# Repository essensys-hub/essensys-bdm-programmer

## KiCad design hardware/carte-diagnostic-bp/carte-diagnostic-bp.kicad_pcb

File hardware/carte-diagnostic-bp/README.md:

# Carte de diagnostic BP

Carte de banc : accès BDM au BP (J33, nappe 10 broches), écoute passive du bus I2C BP↔BA et analyseur 8 voies, derrière un seul port USB-C.

Spécification : `openspec/changes/carte-diagnostic-bp-2026-11-009/`.

**Prototype.** La carte finale est spécifiée par essensys-hub/essensys-i2c-ba-sniffer#10 ; celle-ci sert à valider les connecteurs, la protection 15 V, l'assemblage JLCPCB et la lecture BDM par la nappe.

| Fichier | Rôle |
|---|---|
| `gen_sch.py` | Décrit le circuit (table broche → net) et génère `carte-diagnostic-bp.kicad_sch` |
| `carte-diagnostic-bp.kicad_sch` | Schéma KiCad 10, à ouvrir avec le projet `.kicad_pro` |
| `gen_pcb.py`, `route_pcb.py`, `close_gaps.py` | Placement, routage et finition de `carte-diagnostic-bp.kicad_pcb` |
| `export_fab.py` | Gerber, perçages, nomenclature et placement au format JLCPCB |
| `check_netlist.py` | Invariants de sécurité contrôlés sur la netlist exportée |
| `nomenclature.md` | Références LCSC, stock et prix relevés |
| `protection-port-i2c.md` | Calcul de la protection 15 V du port I2C |

## Variantes

| Variante | Fichiers | Pico | USB |
|---|---|---|---|
| Base | `carte-diagnostic-bp.*` | Soudé à plat (pastilles crénelées et TP2/TP3) | Un seul USB-C, hub CH334R vers le Pico et l'analyseur |
| À trous (`CARTE_VARIANTE=tht`) | `carte-diagnostic-bp-tht.*` | Sur broches traversantes, remplaçable | Deux câbles : le micro-USB du Pico et l'USB-C de la carte pour l'analyseur |

La variante à trous n'a ni hub ni son quartz (61 composants au lieu de 66). Le VBUS de la carte ne rejoint pas le Pico : les deux moitiés ont chacune leur alimentation USB et seules les masses sont communes. Les résistances de prise de l'analyseur passent de 1 kΩ à 10 kΩ, pour qu'une moitié éteinte ne soit pas réalimentée par les signaux de l'autre. Elle ne satisfait pas l'exigence « un seul port USB » de la spécification.

Chaque script prend la variante dans la variable d'environnement `CARTE_VARIANTE` (vide ou `tht`).

## Régénérer et contrôler

    python3 hardware/carte-diagnostic-bp/gen_sch.py
    kicad-cli sch erc --severity-all --exit-code-violations hardware/carte-diagnostic-bp/carte-diagnostic-bp.kicad_sch
    pytest tests/test_carte_diagnostic_netlist.py

## Router la carte

    KPY=/Applications/KiCad/KiCad.app/Contents/Frameworks/Python.framework/Versions/3.9/bin/python3
    kicad-cli sch export netlist --format kicadsexpr -o /tmp/carte.net hardware/carte-diagnostic-bp/carte-diagnostic-bp.kicad_sch
    $KPY hardware/carte-diagnostic-bp/gen_pcb.py /tmp/carte.net            # empreintes, nets, placement, plans internes
    $KPY hardware/carte-diagnostic-bp/route_pcb.py freerouting-2.5.0.jar   # routage Freerouting, plans de masse externes
    $KPY hardware/carte-diagnostic-bp/close_gaps.py                        # ferme les dernières liaisons sous contrôle du DRC

Le routage automatique n'est pas reproductible à l'identique : `carte-diagnostic-bp.kicad_pcb` est versionné tel que routé, et la CI contrôle son DRC sans le régénérer.

## Dossier de fabrication JLCPCB

    python3 hardware/carte-diagnostic-bp/export_fab.py

Le dossier `fab/` (non versionné, publié comme artefact par la CI) contient `gerbers.zip`, `bom-jlcpcb.csv` et `cpl-jlcpcb.csv`. Options de commande : 4 couches, 1,6 mm, assemblage de la face avant. Dans l'outil de commande, contrôler l'aperçu du placement : les rotations viennent de KiCad et certaines pièces (SOT-23, SOT-223, QFN, USB-C) peuvent demander une correction.

Six composants ne sont pas assemblés par JLCPCB (`fab/a-souder-a-la-main.csv`) : le module Pico, l'embase de la nappe, les deux embases I2C, le connecteur SWD et le bouton BOOTSEL, dont la référence reste à figer. Un RP2040 dont la flash est vierge démarre seul en mode de chargement USB : le bouton ne sert qu'aux rechargements suivants.

## État

Les deux variantes font 100 × 60 mm en 4 couches et ont été routées le 2026-11-15 : DRC à 0 violation et 0 liaison manquante, pastilles conformes à la netlist du schéma (301 pour la base, 266 pour la variante à trous). Les repères des petits composants (R, C, D, F) ne sont pas sérigraphiés.

Le routage sort d'un routeur automatique et **doit être relu avant toute commande** : paire USB non routée en différentiel, position du quartz, découplage. Le dossier de fabrication se génère, mais il n'a pas encore été chargé dans l'outil de commande JLCPCB.

Sur la carte de base, les pastilles TP2 et TP3 du module Pico sont sous le module : elles demandent de la pâte à braser et de l'air chaud, ou un perçage de la carte à ajouter.

Défaut connu : le connecteur USB-C (J1) est en retrait d'environ 0,5 mm du bord de la carte ; certains câbles peuvent buter. À rapprocher du bord à la prochaine révision. Dans l'outil JLCPCB, J1 doit aussi être remonté d'environ 1,5 mm pour tomber sur ses pastilles.

À confirmer avant la commande :

- fiche technique du hub CH334R : quartz 12 MHz et broche `RESET/CDP` ;
- empreinte des embases I2C, à confronter au plan Würth 66200421122 (empreinte Micro-Fit 3.0 provisoire) ;
- empreinte du connecteur USB-C KH-TYPE-C-16P ;
- chaîne de capture RP2040 (tâche 1.2).

Sur la carte de base, le micro-USB du module Pico ne doit jamais être branché : son USB passe par les pastilles TP2 et TP3 vers le hub.

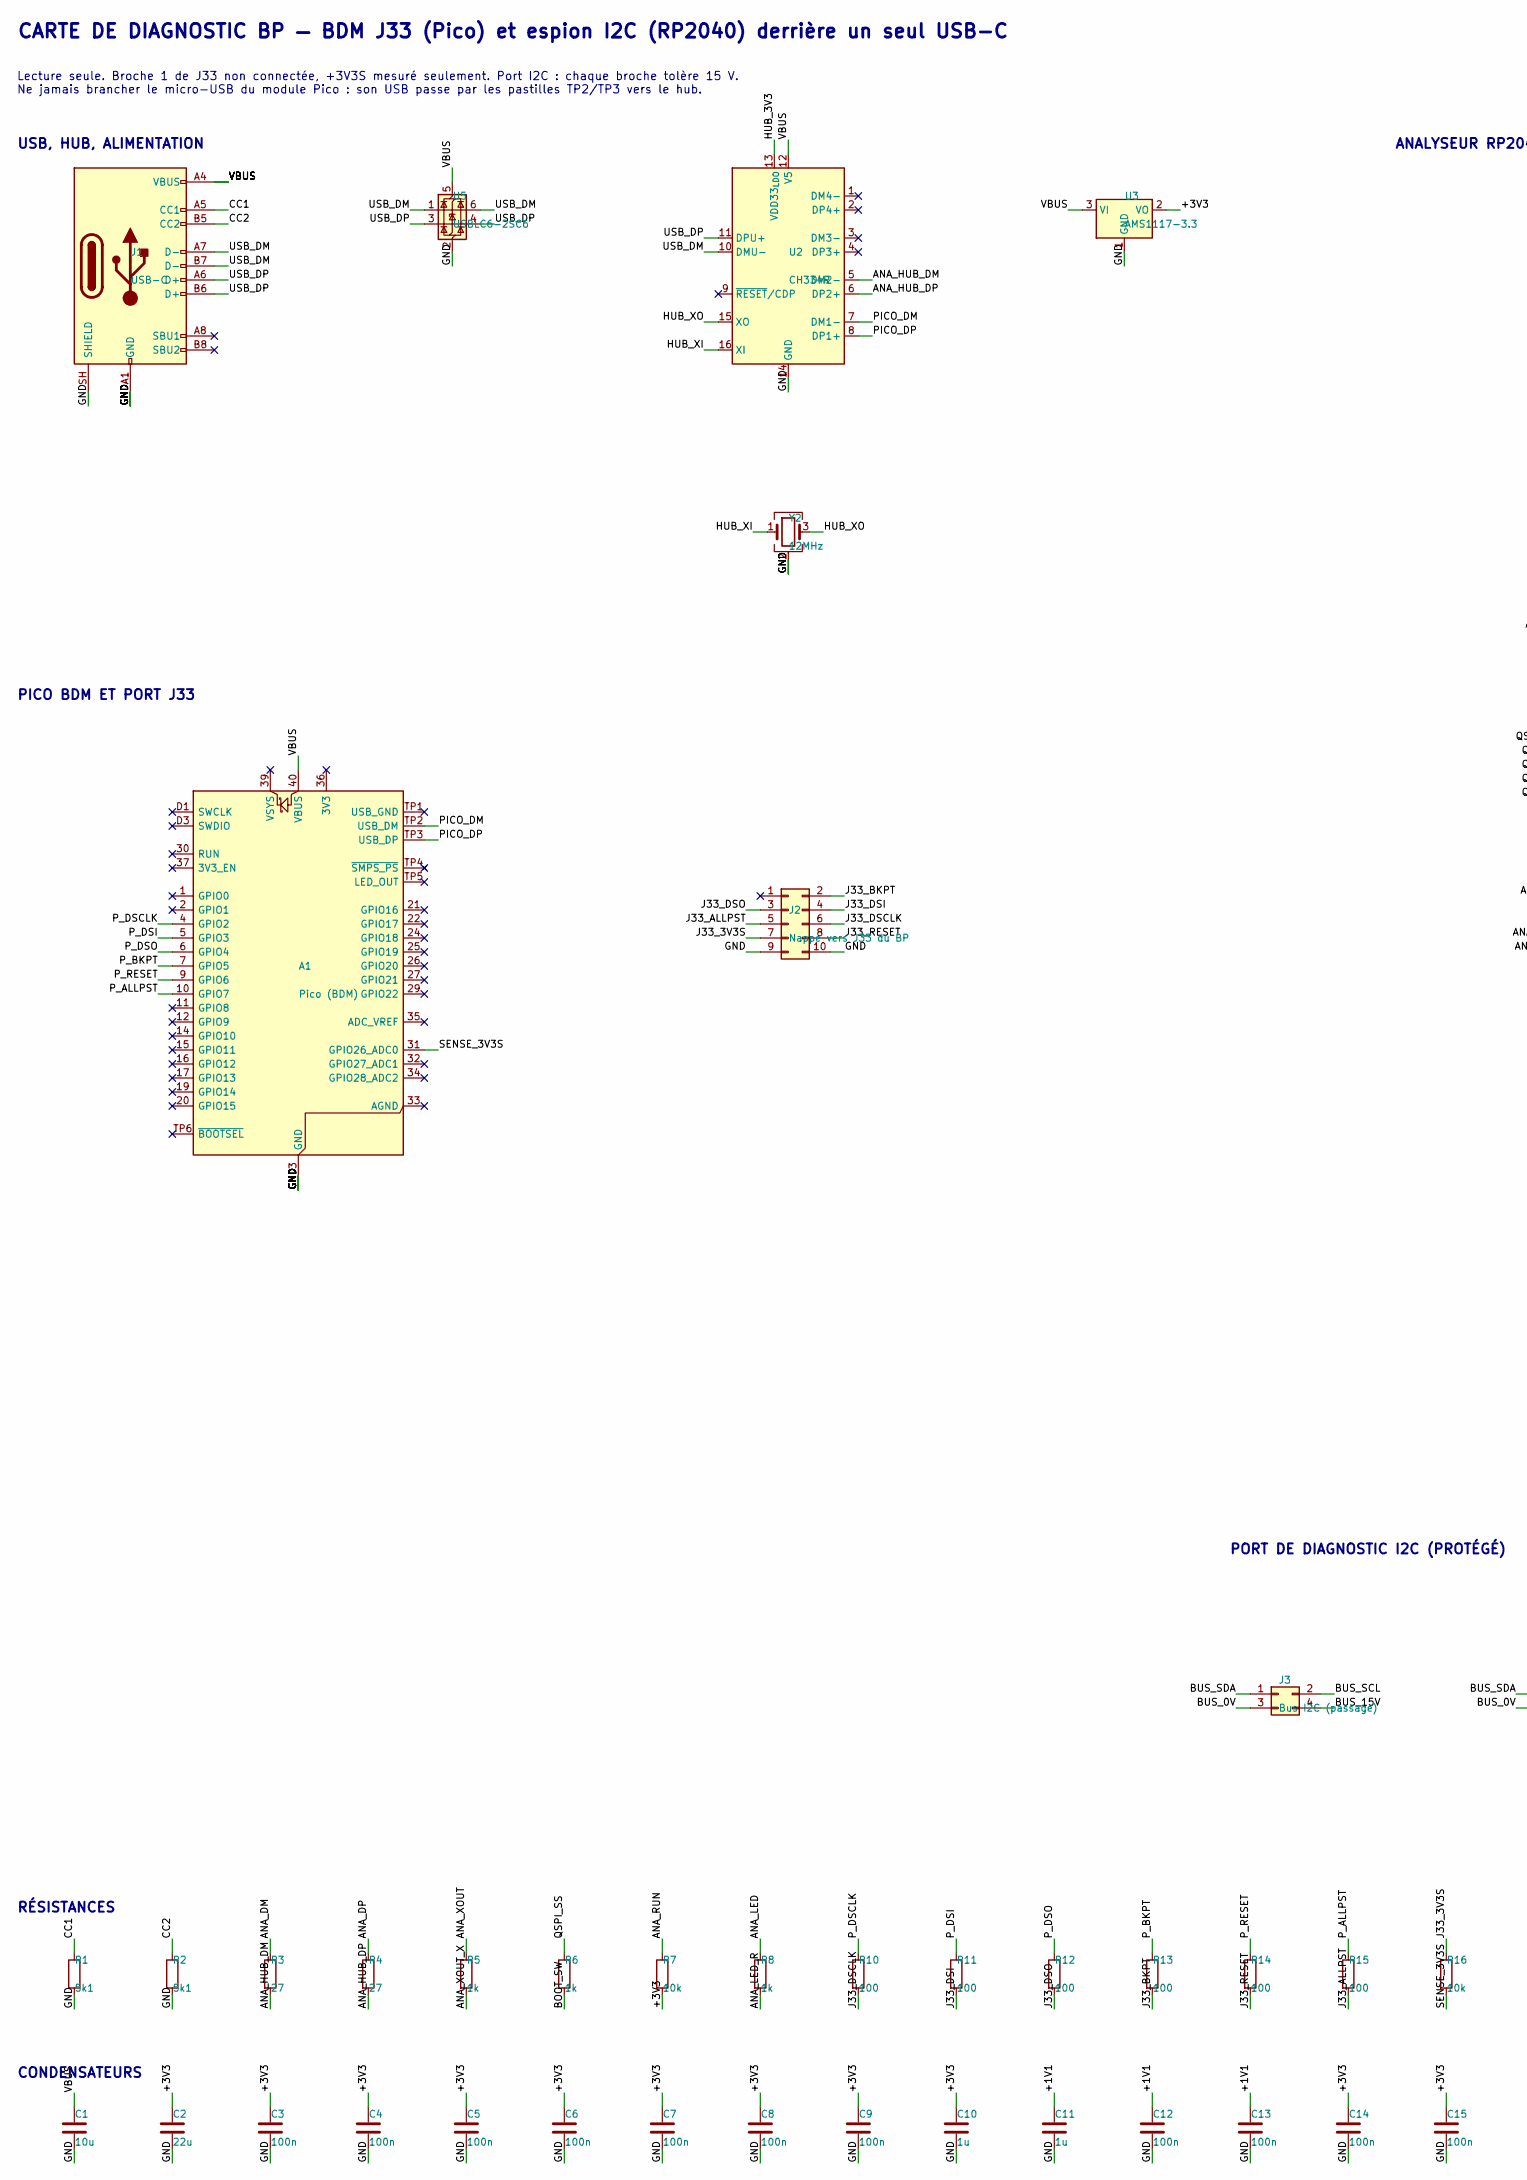
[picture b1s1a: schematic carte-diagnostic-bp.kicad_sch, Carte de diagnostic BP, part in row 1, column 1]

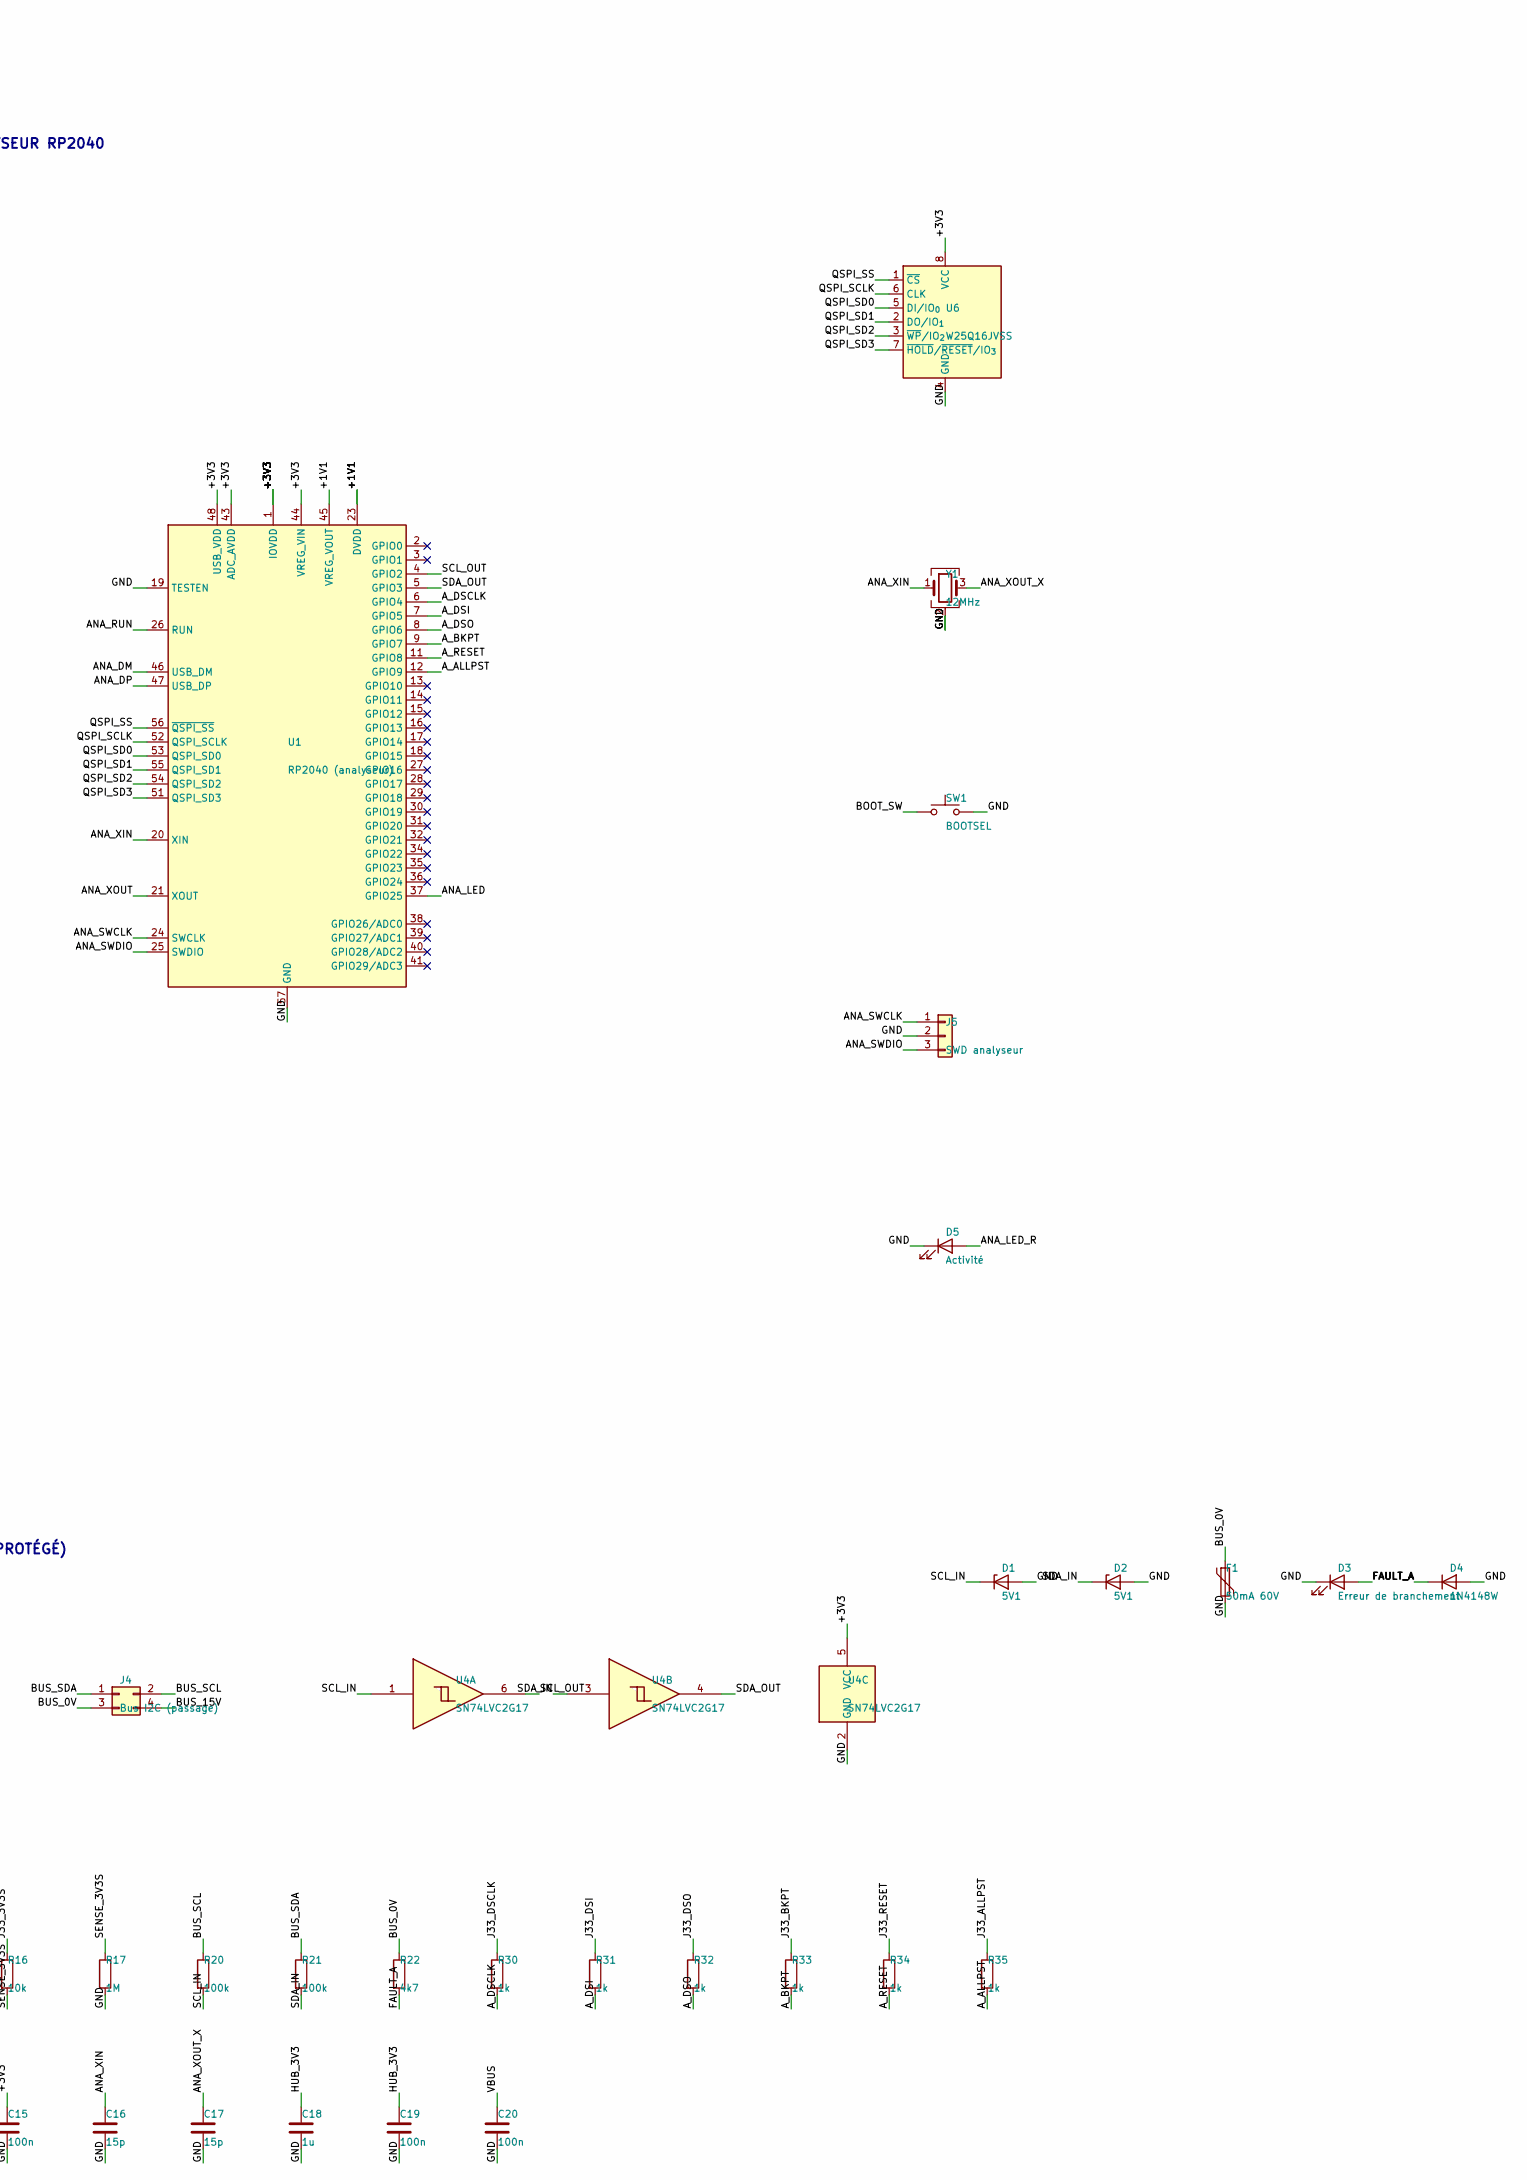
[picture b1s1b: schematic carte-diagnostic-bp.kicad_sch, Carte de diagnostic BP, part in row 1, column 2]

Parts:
A1: Pico (BDM); RaspberryPi_Pico_SMD; LCSC soudé à la main
C1: 10u; C_0603_1608Metric; LCSC C19702
C2: 22u; C_0603_1608Metric; LCSC C59461
C3, C4, C5, C6, C7, C8, C9, C12, C13, C14, C15, C19, C20: 100n; C_0603_1608Metric; LCSC C14663
C10, C11, C18: 1u; C_0603_1608Metric; LCSC C15849
C16, C17: 15p; C_0603_1608Metric; LCSC C1644
D1, D2: 5V1; D_SOD-123; LCSC C19077401
D3: Erreur de branchement; LED_0603_1608Metric; LCSC C2286
D4: 1N4148W; D_SOD-123; LCSC C81598
D5: Activité; LED_0603_1608Metric; LCSC C2286
F1: 50mA 60V; Fuse_1206_3216Metric; LCSC C2830235
J1: USB-C; USB_C_Receptacle_HRO_TYPE-C-31-M-12; LCSC C709357
J2: Nappe vers J33 du BP; IDC-Header_2x05_P2.54mm_Vertical; LCSC soudé à la main
J3, J4: Bus I2C (passage); Molex_Micro-Fit_3.0_43045-0412_2x02_P3.00mm_Vertical; LCSC Würth 66200421122, soudé à la main
J5: SWD analyseur; PinHeader_1x03_P2.54mm_Vertical; LCSC non monté
R1, R2: 5k1; R_0603_1608Metric; LCSC C23186
R3, R4: 27; R_0603_1608Metric; LCSC C25190
R5, R6, R8, R30, R31, R32, R33, R34, R35: 1k; R_0603_1608Metric; LCSC C21190
R7, R16: 10k; R_0603_1608Metric; LCSC C25804
R10, R11, R12, R13, R14, R15: 100; R_0603_1608Metric; LCSC C22775
R17: 1M; R_0603_1608Metric; LCSC C22935
R20, R21: 100k; R_0603_1608Metric; LCSC C25803
R22: 4k7; R_0603_1608Metric; LCSC C23162
SW1: BOOTSEL; SW_SPST_TL3342; LCSC non monté : référence et empreinte à fi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
U1: RP2040 (analyseur); QFN-56-1EP_7x7mm_P0.4mm_EP3.2x3.2mm; LCSC C2040
U2: CH334R; QSOP-16_3.9x4.9mm_P0.635mm; LCSC C4154405
U3: AMS1117-3.3; SOT-223-3_TabPin2; LCSC C6186
U4: SN74LVC2G17; SOT-23-6; LCSC C10429
U5: USBLC6-2SC6; SOT-23-6; LCSC C5261088
U6: W25Q16JVSS; SOIC-8_5.3x5.3mm_P1.27mm; LCSC C131025
Y1, Y2: 12MHz; Crystal_SMD_3225-4Pin_3.2x2.5mm; LCSC C276421

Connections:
+1V1: C11.1, C12.1, C13.1, U1.23 (DVDD), U1.45 (VREG_VOUT), U1.50 (DVDD)
+3V3: C2.1, C3.1, C4.1, C5.1, C6.1, C7.1, C8.1, C9.1, C10.1, C14.1, C15.1, R7.2, U1.1 (IOVDD), U1.10 (IOVDD), U1.22 (IOVDD), U1.33 (IOVDD), U1.42 (IOVDD), U1.43 (ADC_AVDD), U1.44 (VREG_VIN), U1.48 (USB_VDD), U1.49 (IOVDD), U3.2 (VO), U4.5 (VCC), U6.8 (VCC)
ANA_DM: R3.1, U1.46 (USB_DM)
ANA_DP: R4.1, U1.47 (USB_DP)
ANA_HUB_DM: R3.2, U2.5 (DM2-)
ANA_HUB_DP: R4.2, U2.6 (DP2+)
ANA_LED: R8.1, U1.37 (GPIO25)
ANA_LED_R: D5.2 (A), R8.2
ANA_RUN: R7.1, U1.26 (RUN)
ANA_SWCLK: J5.1, U1.24 (SWCLK)
ANA_SWDIO: J5.3, U1.25 (SWDIO)
ANA_XIN: C16.1, U1.20 (XIN), Y1.1
ANA_XOUT: R5.1, U1.21 (XOUT)
ANA_XOUT_X: C17.1, R5.2, Y1.3
A_ALLPST: R35.2, U1.12 (GPIO9)
A_BKPT: R33.2, U1.9 (GPIO7)
A_DSCLK: R30.2, U1.6 (GPIO4)
A_DSI: R31.2, U1.7 (GPIO5)
A_DSO: R32.2, U1.8 (GPIO6)
A_RESET: R34.2, U1.11 (GPIO8)
BOOT_SW: R6.2, SW1.1
BUS_0V: F1.1, J3.3, J4.3, R22.1
BUS_15V: J3.4, J4.4
BUS_SCL: J3.2, J4.2, R20.1
BUS_SDA: J3.1, J4.1, R21.1
CC1: J1.A5 (CC1), R1.1
CC2: J1.B5 (CC2), R2.1
FAULT_A: D3.2 (A), D4.1 (K), R22.2
GND: A1.3 (GND), A1.8 (GND), A1.13 (GND), A1.18 (GND), A1.23 (GND), A1.28 (GND), A1.38 (GND), A1.D2 (GND), C1.2, C2.2, C3.2, C4.2, C5.2, C6.2, C7.2, C8.2, C9.2, C10.2, C11.2, C12.2, C13.2, C14.2, C15.2, C16.2, C17.2, C18.2, C19.2, C20.2, D1.2 (A), D2.2 (A), D3.1 (K), D4.2 (A), D5.1 (K), F1.2, J1.A1 (GND), J1.A12 (GND), J1.B1 (GND), J1.B12 (GND), J1.SH (SHIELD), J2.9, J2.10, J5.2, R1.2, R2.2, R17.2, SW1.2, U1.19 (TESTEN), U1.57 (GND), U2.14 (GND), U3.1 (GND), U4.2 (GND), U5.2 (GND), U6.4 (GND), Y1.2 (G), Y1.4 (G), Y2.2 (G), Y2.4 (G)
HUB_3V3: C18.1, C19.1, U2.13 (VDD33_{LDO})
HUB_XI: U2.16 (XI), Y2.1
HUB_XO: U2.15 (XO), Y2.3
J33_3V3S: J2.7, R16.1
J33_ALLPST: J2.5, R15.2, R35.1
J33_BKPT: J2.2, R13.2, R33.1
J33_DSCLK: J2.6, R10.2, R30.1
J33_DSI: J2.4, R11.2, R31.1
J33_DSO: J2.3, R12.2, R32.1
J33_RESET: J2.8, R14.2, R34.1
PICO_DM: A1.TP2 (USB_DM), U2.7 (DM1-)
PICO_DP: A1.TP3 (USB_DP), U2.8 (DP1+)
P_ALLPST: A1.10 (GPIO7), R15.1
P_BKPT: A1.7 (GPIO5), R13.1
P_DSCLK: A1.4 (GPIO2), R10.1
P_DSI: A1.5 (GPIO3), R11.1
P_DSO: A1.6 (GPIO4), R12.1
P_RESET: A1.9 (GPIO6), R14.1
QSPI_SCLK: U1.52 (QSPI_SCLK), U6.6 (CLK)
QSPI_SD0: U1.53 (QSPI_SD0), U6.5 (DI/IO_{0})
QSPI_SD1: U1.55 (QSPI_SD1), U6.2 (DO/IO_{1})
QSPI_SD2: U1.54 (QSPI_SD2), U6.3 (~WP/IO_{2})
QSPI_SD3: U1.51 (QSPI_SD3), U6.7 (~HOLD/~RESET/IO_{3})
QSPI_SS: R6.1, U1.56 (~QSPI_SS), U6.1 (~CS)
SCL_IN: D1.1 (K), R20.2, U4.1
SCL_OUT: U1.4 (GPIO2), U4.6
SDA_IN: D2.1 (K), R21.2, U4.3
SDA_OUT: U1.5 (GPIO3), U4.4
SENSE_3V3S: A1.31 (GPIO26_ADC0), R16.2, R17.1
USB_DM: J1.A7 (D-), J1.B7 (D-), U2.10 (DMU-), U5.1 (I/O1), U5.6 (I/O1)
USB_DP: J1.A6 (D+), J1.B6 (D+), U2.11 (DPU+), U5.3 (I/O2), U5.4 (I/O2)
VBUS: A1.40 (VBUS), C1.1, C20.1, J1.A4 (VBUS), J1.A9 (VBUS), J1.B4 (VBUS), J1.B9 (VBUS), U2.12 (V5), U3.3 (VI), U5.5 (VBUS)

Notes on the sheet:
CARTE DE DIAGNOSTIC BP — BDM J33 (Pico) et espion I2C (RP2040) derrière un seul USB-C
Lecture seule. Broche 1 de J33 non connectée, +3V3S mesuré seulement. Port I2C : chaque broche tolère 15 V. Ne jamais brancher le micro-USB du module Pico : son USB passe par les pastilles TP2/TP3 vers le hub.
USB, HUB, ALIMENTATION
PICO BDM ET PORT J33
ANALYSEUR RP2040
PORT DE DIAGNOSTIC I2C (PROTÉGÉ)
RÉSISTANCES
CONDENSATEURS

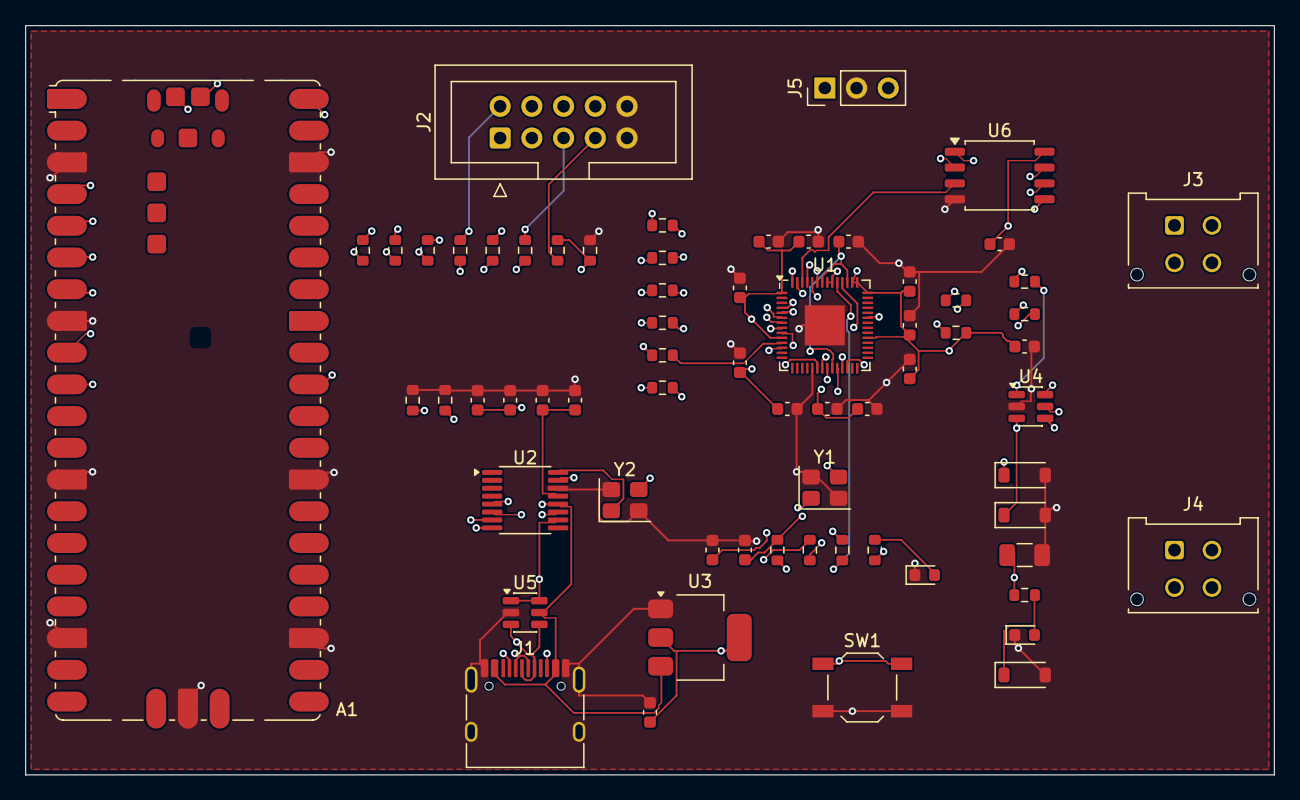
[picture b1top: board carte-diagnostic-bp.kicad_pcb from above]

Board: 4 copper layers, 100.0 x 60.0 mm, 66 parts (0 on the bottom side), 61 nets.
